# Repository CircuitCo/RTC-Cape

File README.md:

RTC-Cape
========
The RTC Cape provides time tracking capability for the BeagleBone Black even when the power is lost. This cape features the DS1338 I2C-based real-time clock/calendar and a holder for a coin battery type CR2032. Setup, reading, and setting up time is easy with the provided device tree overlay.

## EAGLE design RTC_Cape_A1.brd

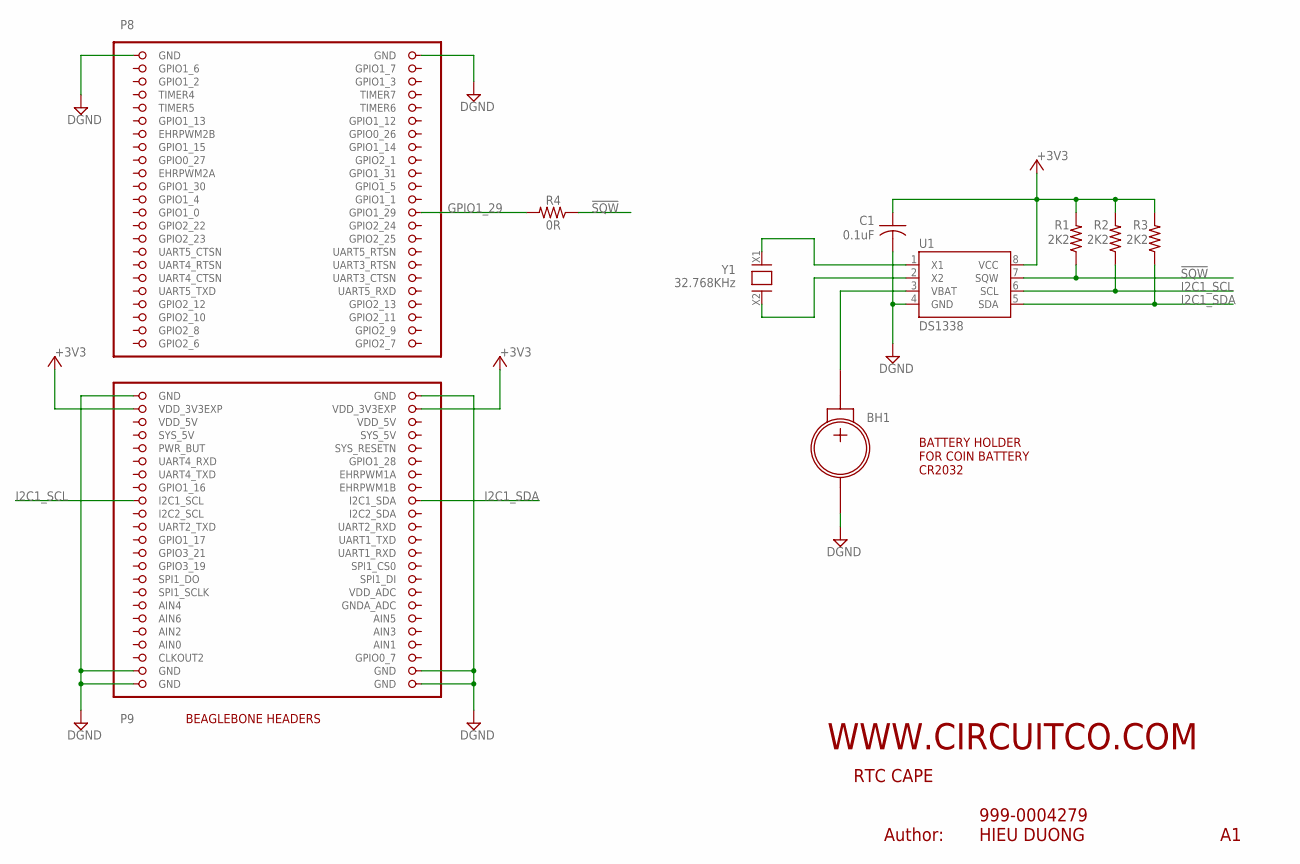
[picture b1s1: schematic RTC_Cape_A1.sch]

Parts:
BH1: BS-7
C1: 0.1uF; C0402
R1, R2, R3: 2K2; R0402
R4: 0R; R0402
U1: DS1338; MXM-SOIC8-90-0112
U$1: BB_OL_GENPROTO
Y1: 32.768KHz; CRYSTAL-CFS-308-SMD

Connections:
!SQW: R1.1, R4.1, U1.7 (SQW)
+3V3: C1.1, R1.2, R2.2, R3.2, U1.8 (VCC), U$1.49 (VDD_3V3EXP), U$1.50 (VDD_3V3EXP)
AIN0: U$1.85 (AIN0)
DGND: BH1.NEG, C1.2, U1.4 (GND), U$1.1 (GND), U$1.2 (GND), U$1.47 (GND), U$1.48 (GND), U$1.89 (GND), U$1.90 (GND), U$1.91 (GND), U$1.92 (GND)
GPIO1_29: R4.2, U$1.26 (GPIO1_29)
I2C1_SCL: R2.1, U1.6 (SCL), U$1.63 (I2C1_SCL)
I2C1_SDA: R3.1, U1.5 (SDA), U$1.64 (I2C1_SDA)
unnamed: BH1.POS, U1.3 (VBAT)
unnamed: U1.2 (X2), Y1.X2 (2)
unnamed: U1.1 (X1), Y1.X1 (1)
SYS_5V: U$1.53 (SYS_5V)
VDD_5V: U$1.51 (VDD_5V), U$1.52 (VDD_5V)

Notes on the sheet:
BATTERY HOLDER FOR COIN BATTERY CR2032
BEAGLEBONE HEADERS
Author:

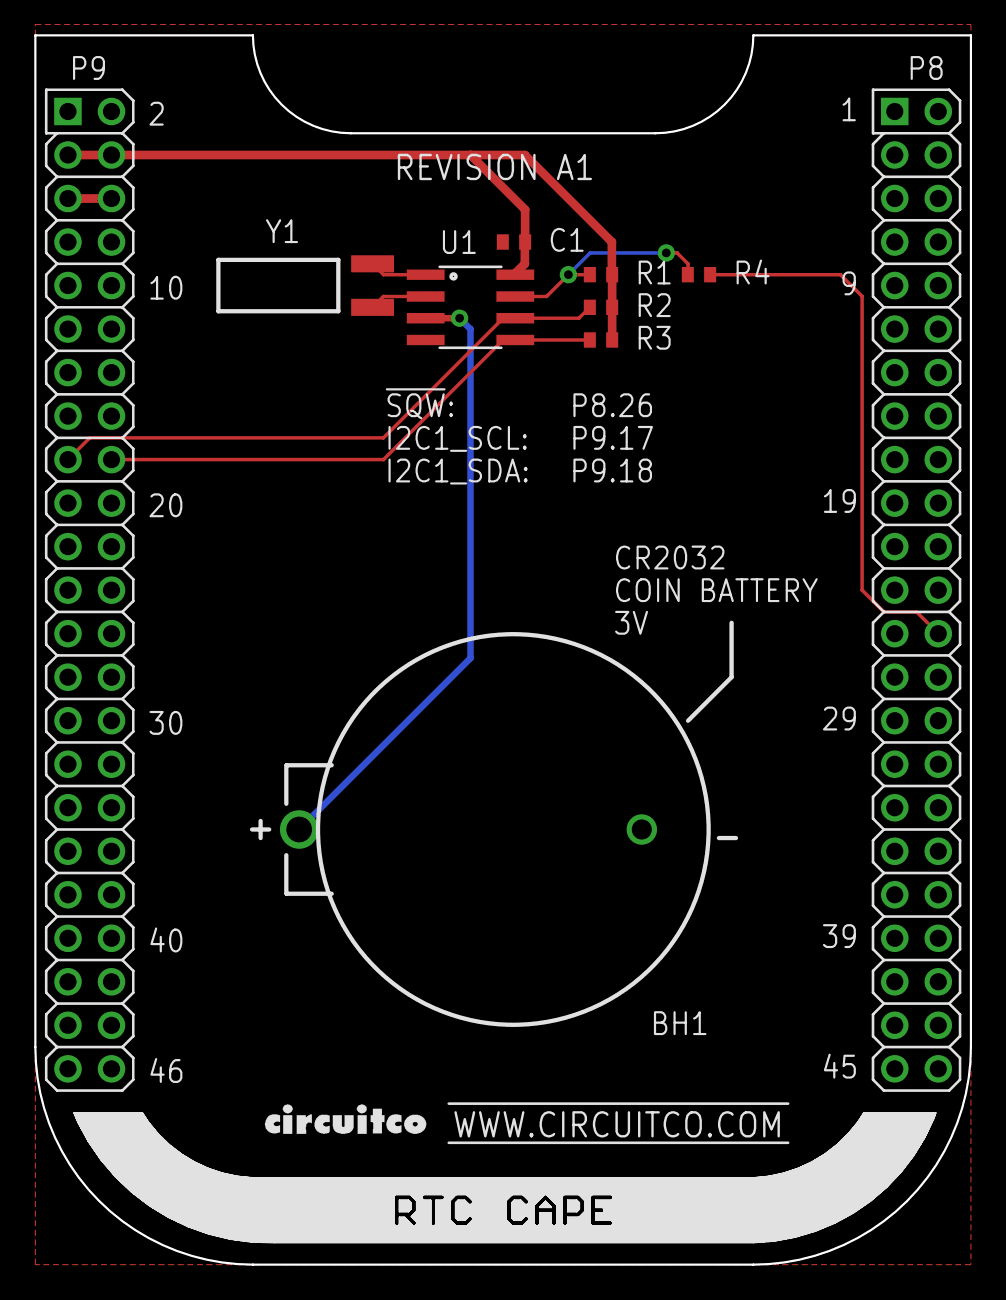
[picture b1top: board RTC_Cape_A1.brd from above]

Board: 2 copper layers, 54.6 x 71.8 mm, 12 parts (0 on the bottom side), 10 nets.

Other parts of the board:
DRILEGEND: DRILEGEND
U$2: CIRCUITCO-LOGO
U$3: NEGA-RTC-NAME

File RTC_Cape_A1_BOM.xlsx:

BOARD NAME: RTC CAPE
REVISION: A1 |  |  |  | LAST UPDATE: | 41733
PART NUMBER: 999-0004279
ITM | QTY | REF DESIGNATOR | PART NUMBER | DESCRIPTION | MANUFACTURER | MAN P/N
1 | 1 | PCB | 999-0004279 | RTC CAPE | CIRCUITCO
2 | 1 | BH1 | 253-0004977 | HOLDER COINCELL 2032 RETAINRCLIP | MPD | BS-7
3 | 1 | C1 | 123-0001047 | CAP CER 0.1UF 10V 10% X5R 0402 | MURATA | GRM155R61A104KA01
4 | 2 | P8, P9 | 235-0002217 | 46 POS,DUAL,GOLD,.1" | MLE | SSHQ-123-D-08-G-LF
5 | 3 | R1, R2, R3 | 110-0001987 | RES 2.2K OHM 1/16W 5% 0402 SMD | YAGEO | RC0402JR-072K2L
6 | 1 | R4 | RC0402JR-070RL | RES 0.0 OHM 1/16W JUMP 0402 SMD | YAGEO | RC0402JR-070RL
7 | 1 | U1 | 140-0004976 | IC RTC SERIAL 512K 8SOIC | MAXIM | DS1338Z-33+
8 | 1 | Y1 | 145-0003173 | CRYSTAL 32.768KHZ 12.5PF THRU | CITIZEN | CFS308-32.768KDZF-UB

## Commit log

2014-06-04 device tree files
2014-06-04 add design files
